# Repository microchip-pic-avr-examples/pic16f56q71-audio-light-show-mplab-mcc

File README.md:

# Audio Light Show Using PIC18-Q71

This project shows the functionality behind a real-time audio processing light show built extremely efficiently on a PIC18-Q71 microcontroller (MCU). 90% of the functionality runs on the MCU without engaging the CPU through the use of various Core-Independent Peripherals (CIPs).

The PIC18-Q71 on-chip analog, consisting of the Operational Amplifier ([OPA](https://www.microchip.com/en-us/products/microcontrollers-and-microprocessors/8-bit-mcus/core-independent-and-analog-peripherals/integrated-analog/operational-amplifier)) and Analog-to-Digital Converter ([ADC](https://www.microchip.com/en-us/products/microcontrollers-and-microprocessors/8-bit-mcus/core-independent-and-analog-peripherals/integrated-analog/analog-to-digital-converter)) modules, measure the incoming analog frequencies and use Direct Memory Access ([DMA](https://www.microchip.com/en-us/products/microcontrollers-and-microprocessors/8-bit-mcus/core-independent-and-analog-peripherals/system-flexibility/direct-memory-access)) to transfer the readings into the Universal Asynchronous Receiver and Transmitter ([UART](https://www.microchip.com/en-us/products/microcontrollers-and-microprocessors/8-bit-mcus/core-independent-and-analog-peripherals/communication-connectivity-peripherals/uart-peripherals))/[DMX512](https://www.microchip.com/en-us/products/microcontrollers-and-microprocessors/8-bit-mcus/core-independent-and-analog-peripherals/communication-connectivity-peripherals/uart-peripherals) module to transmit to the receivers. Each receiver also uses a PIC18-Q71 to receive the DMX data and then appropriately drives WS2812 LEDs through its Serial Peripherals Interface ([SPI](https://www.microchip.com/en-us/products/microcontrollers-and-microprocessors/8-bit-mcus/core-independent-and-analog-peripherals/communication-connectivity-peripherals/spi-peripherals)) module. The receivers are daisy-chained through ethernet cables that transfer both data and power.

The first image below displays seven receviers responding to music, while the other one shows a standby effect. The transmitter has an AUX cable plugged in off-screen.

## Related Documentation

- [PIC18-Q71 Data Sheet](https://ww1.microchip.com/downloads/aemDocuments/documents/MCU08/ProductDocuments/DataSheets/PIC18F26-46-56Q71-Microcontroller-Data-Sheet-DS40002329.pdf)
- [TB3204 - DMX-512 using the UART with Protocol Support](https://ww1.microchip.com/downloads/en/Appnotes/TB3204-DMX-512-using-UART-90003204A.pdf) - Setting up DMX with DMA on a PIC18
- [PIC18F56Q71 Curiosity Nano Hardware User Guide](https://ww1.microchip.com/downloads/aemDocuments/documents/MCU08/ProductDocuments/UserGuides/PIC18F56Q71-CuriosityNano-HW-UG-DS50003481.pdf) - Development tools documentation
- [MIC28517 Data Sheet](https://ww1.microchip.com/downloads/aemDocuments/documents/APID/ProductDocuments/DataSheets/MIC28517-Data-Sheet-DS20006317C.pdf) - Voltage Converter Data Sheet 

## Software Used

- [MPLAB® X IDE 6.1.5](https://www.microchip.com/en-us/development-tools-tools-and-software/mplab-x-ide?utm_source=GitHub&utm_medium=TextLink&utm_campaign=MCU8_MMTCha_MPAE_Examples&utm_content=pic16f56q71-dmx-light-show-github) or newer
- [MPLAB XC8 2.45.0](https://www.microchip.com/en-us/development-tools-tools-and-software/mplab-xc-compilers?utm_source=GitHub&utm_medium=TextLink&utm_campaign=MCU8_MMTCha_MPAE_Examples&utm_content=pic16f56q71-dmx-light-show-github) or newer
- [MPLAB Code Configurator (MCC) 3.95.0](https://www.microchip.com/mplab/mplab-code-configurator) or newer

## Setup

To operate the demo, connect all the transmitters and receivers with an Ethernet cable. Power up the transmitter with a 48V power supply and connect an AUX cable to watch the incoming audio signal come to life. Each receiver is selectively listening to specific DMX data. A DIP switch on each receiver dictates what incoming DMX data to listen to, effectively defining a node number.

Apart from the final transmitter and receiver boards shown in the initial image representations, 3D printed stands are also shown which are used to mount the receiver boards and the diffusing tubes. The diffusing tubes consist of WS2812 LEDs taped to an aluminum strip for support. Inside the fluorescent tube guard, parchment paper lines the interiors and a 3D printed cap securely holds the aluminum strip towards the back of the tube ensuring optimal LED diffusion.

## Theory of Operation

This demo can be broken up into three portions:
* [Audio Signal Processing](#audio-signal-processing)
* [DMX Data](#dmx-data)
* [Driving the WS2812 LEDs](#driving-the-ws2812-leds)

The distinguishing feature of this project is nearly all of this demo operates without the CPU, and instead using CIPs and the DMA. The CPU's sole task is to run the manually programmed visual effects that convert the acquired frequency data into LED data.

### Audio Signal Processing
To obtain the initial audio data, this project extracts bins of audio frequencies and performs peak detection on each bin giving a value corresponding to the intensity of the audio frequency. Each peak is then visually represented on a different LED tube.

Source: [MSGEQ7 data sheet](https://www.sparkfun.com/datasheets/Components/General/MSGEQ7.pdf)

To extract and acquire these audio frequency bins, analog bandpass filters with an ADC can be used for each desired frequency. Alternatively, an MSGEQ7 chip was used to reduce the number of needed passive components. This chip functions as a bandpass filter, multiplexing between frequencies. The PIC18-Q71 drives the chip to change where the center frequency is and then uses its on-board ADC to sample the peak. The PIC18-Q71's OPA is used in Unity Gain mode to impedance match the output, then the ADC with computation is used to acquire the output peak.

By using the OPA in Unity Gain mode, a buffer is created that ensures the ADC can read the analog signal without affecting it. If the input from the filters is of high impedance, the ADC may not read the result accurately. By using the OPA as a buffer, this ensures the ADC can always read the signal accurately and without affecting the original signal. Also, the ADC has built-in computation that provides an automatic average of readings to eliminate potential outliers, providing a more accurate reading.

### DMX Data
DMX512, or DMX for short, is an industry-standard protocol commonly used to control stage lighting and theatrical effects, providing centralized control of multiple devices from a single controller. Devices in a DMX network are daisy-chained together creating a "DMX universe". Within each universe, each node listens to the start code and specific data bytes out of the 512 bytes in each packet.

For this DMX light show, each node listens to 3 bytes and the start code. Depending on the start code, the nodes interpret their three bytes differently, giving DMX flexibility on the fly.

| Start Code | Mode | Byte 1 | Byte 2 | Byte 3 |
| ---- | ---- | ---- | ---- | ---- |
| 2 | Reactive | G LED Data  | R LED Data | B LED Data |
| 3 | Visualizer | # of LEDs to Turn On | Color Change Threshold 1 | Color Change Threshold 2 |

 When `Start Code = 2`, each byte represents the entire tube's RGB data. For the first receiver, when `Start Code = 2` and the data are as shown above (`G = 255, R = 0, B = 0`), the tube looks like in the left image. When `Start Code = 3`, the data interpretation is altered to the table below and the tube for receiver 1 changes to what is shown in the image on the right.

DMX provides the needed structure for fast and flexible data. The PIC18-Q71 compliments DMX by allowing the data's meaning to be changed based on Input/Output (I/O). The data interpretation is changed by toggling a switch, which changes the start code.

### Driving the WS2812 LEDs
After the DMX data has been received, the WS2812 LEDs change to reflect the incoming data. WS2812 LEDs are programmable through a 1-Wire protocol. The LEDs are daisy-chained together, similar to the DMX protocol, but each LED receives all the data, strips off its portion, and sends the data onward. The data for each LED consists of one byte for G, R, and B data respectively (for a total of three bytes).

To drive the WS2812 protocol, the microcontroller pulls a line high or low for different amounts of time:

This requires an I/O line to be changed every 220 ns or at least 4.5 million times per second requiring 4.5 Mhz of processing power. This could create a processing bottleneck in time-sensitive applications. Alternatively, the SPI module of the PIC18-Q71 device family can creatively drive the WS2812 protocol in hardware, so that the MCU simply needs to load the SPI buffer with multiple data bytes instead of individually driving each bit. This is done by chaining the SPI module with the PWM and Configurable Logic Cell (CLC) CIPs to create the serial output needed by the WS2812 protocol.

*SPI + PWM + CLC Waveform*

Implementation with CLC's - Generating 0's

Implementation with CLC's - Generating 1's

## Development Hardware Used

For a large-scale project that shows many moving parts working together, it helps to first set up using easy-to-use hardware, then transition to something more polished and stable.

This project was first set up using [Curiosity Development boards](https://www.microchip.com/en-us/tools-resources/evaluation-boards/curiosity) and jumper wires. Curiosity Development boards feature an on-board programmer, meaning that only a USB cable was needed to program each PIC18-Q71. As the features were developed and the hardware requirements stopped changing, the project was transitioned to dedicated PCBs. Below is the main hardware used for the initial prototype.

- PIC18F56Q71 Curiosity Nano ([EV01G21A](https://www.microchip.com/en-us/development-tool/EV01G21A))
- Curiosity Nano Base for Click Boards™ ([AC164162](https://www.microchip.com/en-us/development-tool/ac164162))
- [MSGEQ7 Graphic Equalizer Display Filter](https://www.sparkfun.com/products/10468)
- [WS2812 LED Strip](https://www.amazon.com/BTF-LIGHTING-Waterproof-Flexible-Individually-Addressable/dp/B01CDTEEZ2/)

The perfboard held the supporting circuitry for the MSGEQ7 to acquire the analog signal. After the analog signal was acquired, a single-ended signal transmitted the DMX data to the receiver board which drive the WS2812 LED, as shown on the left. One other notable point is the Curiosity Nanos all needed to connect to A/C power, greatly limiting the decentralized nature of the daisy-chained DMX protocol. The PIC18F56Q71 was used since it is the family variation used on the Curiosity Nano boards, but any PIC18-Q71 can be used for the project, provided the pin output settings were changed in the code.

The final design was built on PCBs that encoded the DMX signal per the DMX specification, using RS-485 differential signaling for signal integrity of up to 4,000 feet. Also, instead of using XLR cables for the DMX signal, Ethernet cables were used, enabling Power over Ethernet (PoE) to be run through the same cable, eliminating the central power source requirement. This allows only one connection to a power source and large cable runs for the demo to be set up across a stage or even a room - perfect for traveling musicians who need to set up and tear down their equipment quickly.

## Final Hardware Used

- [MPLAB PICkit™ 5 In-Circuit Debugger](https://www.microchip.com/en-us/development-tool/pg164150)

### The Transmitter
The transmitter was built on a custom 4-layer PCB. All parts used are in the [Transmitter Bill of Materials](./PCBs/DMX%20Transmitter/dmxTxBOM.csv) in this repository, as well as all of the corresponding [files needed to have the boards manufactured](./PCBs/DMX%20Transmitter/dmxTx-Outputs.zip). Similar to the prototype hardware, the audio signal comes in and the PIC18-Q71 processes it and sends out the DMX data, but this time, it does so on an Ethernet cable. As noted above, passive PoE was implemented so a 48V power source is used and a MIC28517 buck converter steps down the voltage to the MCU's required five volts.

Notable parts in each of the section of the board:

## Analog In
 The [MSGEQ7](https://www.sparkfun.com/products/10468) extracts the amplitudes of seven frequency bands from an audio signal to be displayed.

## PIC18-Q71
The [PIC18-Q71](https://www.microchip.com/en-us/products/microcontrollers-and-microprocessors/8-bit-mcus/pic-mcus/pic18-q71) drives and reads the MSGEQ7 output by first matching the analog impedance using its on-chip OPA as a unity gain buffer, then sampling the signal using its ADC. It then sends out lighting data to each of the receiver nodes over DMX.

## 48 to 5V
The [MIC28517](https://www.microchip.com/en-us/product/mic28517) was chosen since it can handle the 48V requirements of PoE while providing up to 8A. Each receiver node needs up to 1.5A for the WS2812 LEDs, so this chip gives us plenty of overhead.

## SP485
This chip converts the outgoing DMX signal into a differential pair (RS-485) for increased signal distance (U3 on schematic).

### The Receivers
The receiver [Bill of Materials](./PCBs/DMX%20Receiver/dmxRx.csv) and [board files](./PCBs/DMX%20Receiver/dmxRx-v2Outputs.zip) are included in this repository. The receivers function the same as in the prototype, but have Ethernet connectors on either side pass through the power and DMX signals to continue the daisy chain. The PIC18-Q71 on each receiver takes the DMX data in and then appropriately drives the WS2812 LEDs using its CIPs. Each receiver is programmed using a PICkit™ 5 programmer, as opposed to the on-board PKOB programmer on the Curiosity Nanos used during development.

## Summary
This project covered the theory and functional implementation of a real-time audio light show using the PIC18-Q71. It provides the foundation for scaling this idea into a full-scale application or modifying it as needed.

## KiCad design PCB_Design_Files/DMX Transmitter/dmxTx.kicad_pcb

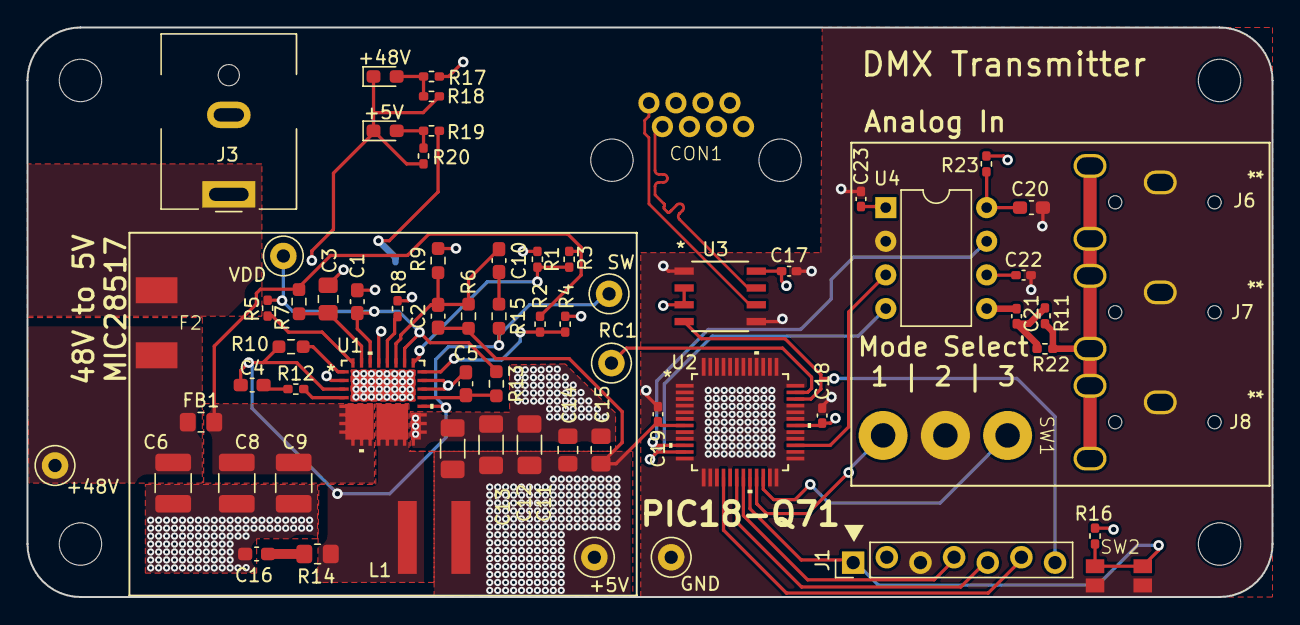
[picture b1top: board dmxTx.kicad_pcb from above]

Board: 4 copper layers, 94.0 x 43.0 mm, 72 parts (1 on the bottom side), 40 nets.

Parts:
C1, C5: 4.7uF; C_0603_1608Metric_Pad1.08x0.95mm_HandSolder
C2: 4700pF; C_0603_1608Metric_Pad1.08x0.95mm_HandSolder
C3: 1uF; C_0805_2012Metric_Pad1.18x1.45mm_HandSolder
C4, C10: 0.1uF; C_0603_1608Metric_Pad1.08x0.95mm_HandSolder
C6, C8, C9: 10uF; C_1210_3225Metric_Pad1.33x2.70mm_HandSolder
C11, C12, C13: 100uF; C_1206_3216Metric_Pad1.33x1.80mm_HandSolder
C14, C15: 22uF; C_0805_2012Metric_Pad1.18x1.45mm_HandSolder
C16: 1000pF; C_0603_1608Metric_Pad1.08x0.95mm_HandSolder
C17, C18, C19, C22, C23: 0.1u; C_0402_1005Metric_Pad0.74x0.62mm_HandSolder
C20: 33p; C_0603_1608Metric_Pad1.08x0.95mm_HandSolder
C21: 0.01u; C_0402_1005Metric_Pad0.74x0.62mm_HandSolder
CON1: E5J88-00LJG2-L
D1: +48V; LED_0603_1608Metric_Pad1.05x0.95mm_HandSolder
D2: +5V; LED_0603_1608Metric_Pad1.05x0.95mm_HandSolder
F1: High Amp; 0679L9100-05
F2: Low Amp; 0679L9100-05
FB1: 120R; R_0805_2012Metric_Pad1.20x1.40mm_HandSolder
H1, H2, H3, H4: MountingHole; MountingHole_3.2mm_M3
J1: Conn_01x07_Socket; PinHeader_1x07_P2.54mm_Vertical
J3: Jack-DC; BarrelJack_CUI_PJ-063AH_Horizontal
J6, J7, J8: STX-3000; STX-3000_KYC
L1: 3.3uH; XGL6060
R1: 300k; R_0402_1005Metric_Pad0.72x0.64mm_HandSolder
R2, R3, R5: 100k; R_0402_1005Metric_Pad0.72x0.64mm_HandSolder
R4, R8, R12: 0R; R_0402_1005Metric_Pad0.72x0.64mm_HandSolder
R6: 10k; R_0603_1608Metric_Pad0.98x0.95mm_HandSolder
R7, R13: 1R; R_0603_1608Metric_Pad0.98x0.95mm_HandSolder
R9: 1.37k; R_0603_1608Metric_Pad0.98x0.95mm_HandSolder
R10: 3.01k; R_0603_1608Metric_Pad0.98x0.95mm_HandSolder
R11, R22: 11k; R_0402_1005Metric_Pad0.72x0.64mm_HandSolder
R14: 1R; R_0805_2012Metric_Pad1.20x1.40mm_HandSolder
R15: 24.9k; R_0603_1608Metric_Pad0.98x0.95mm_HandSolder
R16: 10k; R_0402_1005Metric_Pad0.72x0.64mm_HandSolder
R17, R19: 1k; R_0402_1005Metric_Pad0.72x0.64mm_HandSolder
R18: 47; R_0402_1005Metric_Pad0.72x0.64mm_HandSolder
R20: 790; R_0402_1005Metric_Pad0.72x0.64mm_HandSolder
R23: 200k; R_0402_1005Metric_Pad0.72x0.64mm_HandSolder
SW1: SW_SPDT_MSM; 100AWDP1T2B4M2QE
SW2: MCLR_SW; EVQ-P7A01P
TP1: SW; TestPoint_Loop_D2.50mm_Drill1.0mm
TP2: VDD; TestPoint_Loop_D2.50mm_Drill1.0mm
TP3: RC1; TestPoint_Loop_D2.50mm_Drill1.0mm
TP5: +48V; TestPoint_Loop_D2.50mm_Drill1.0mm
TP9: +5V; TestPoint_Loop_D2.50mm_Drill1.0mm
TP10: GND; TestPoint_Loop_D2.50mm_Drill1.0mm
U1: MIC28517T-E/PHA; VQFN32_6X6_3EP_PHA_MCH
U2: PIC18F56Q71-I/PT; TQFP48_PT_MCH
U3: SP485CN-L; NSOIC-8
U4: MSGEQ7; DIP-8_W7.62mm

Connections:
+5V: C2.1, C11.1, C12.1, C13.1, C14.1, C15.1, C17.2, C18.2, C19.2, C23.2, J1.2, L1.2, R6.2, R16.1, R19.2, R23.2, TP9.1, U2.7 (VDD), U2.30 (VDD), U3.2 (*RE), U3.3 (DE), U3.8 (VCC), U4.1 (VDD)
+48V: C6.1, F2.2, FB1.1, TP5.1
+48V_Hi_Amp: CON1.6, CON1.7, CON1.8, F1.2, R17.2
AGND: C1.2, C3.2, C5.2, C6.2, C8.2, C9.2, C11.2, C12.2, C13.2, C14.2, C15.2, C16.2, C17.1, C18.1, C19.1, C20.1, C22.2, C23.1, CON1.3, CON1.4, CON1.5, D1.1 (K), D2.1 (K), J1.3, J3.2, J6.1, J7.1, J8.1, R1.2, R4.1, R8.1, R9.1, R18.1, R20.1, SW1.2, SW2.2, TP10.1, U1.2 (PGND), U1.16 (PGND), U1.17 (PGND), U1.18 (PGND), U1.19 (PGND), U1.22 (PGND), U1.23 (EXTVDD), U1.29 (PGND), U1.33 (PGND), U1.EP19 (PGND), U2.1 (RC7), U2.2 (RD4), U2.3 (RD5), U2.4 (RD6), U2.5 (RD7), U2.6 (VSS), U2.8 (RB0), U2.9 (RB1), U2.12 (RF4), U2.13 (RF5), U2.14 (RF6), U2.15 (RF7), U2.17 (RB5), U2.23 (RA2), U2.24 (RA3), U2.25 (RA4), U2.26 (RA5), U2.28 (RE1), U2.29 (RE2), U2.31 (VSS), U2.32 (RA7), U2.33 (RA6), U2.36 (RF0), U2.37 (RF1), U2.38 (RF2), U2.39 (RF3), U2.40 (RC2), U2.41 (RC3), U2.42 (RD0), U2.43 (RD1), U2.44 (RD2), U2.45 (RD3), U2.46 (RC4), U2.47 (RC5), U2.48 (RC6), U3.1 (RO), U3.5 (GND), U4.2 (VSS)
AN_OUT: U2.27 (RE0), U4.3 (OUT)
AUDIO_IN: J6.2, J6.3, J7.2, J7.3, J8.2, J8.3, R11.1, R22.1
D+: CON1.1, U3.6 (A)
D-: CON1.2, U3.7 (B)
DMX OUT: J1.7, U2.34 (RC0), U3.4 (DI)
FB: C2.2, C10.2, R6.1, R9.2, U1.27 (FB)
ICSPCLK: J1.5, U2.18 (RB6/ICSPCLK)
ICSPDAT: J1.4, U2.19 (RB7/ICSPDAT)
ILIM: R10.2, U1.1 (ILIM)
MCLR: J1.1, R16.2, SW2.1, U2.20 (RE3/*MCLR/VPP)
MODE1: SW1.1, U2.21 (RA0)
MODE2: SW1.3, U2.22 (RA1)
unnamed: C4.1, R12.1
unnamed: C10.1, R15.1
unnamed: C16.1, R14.1
unnamed: C21.1, R11.2, R22.2
unnamed: D1.2 (A), R17.1, R18.2
unnamed: D2.2 (A), R19.1, R20.2
unnamed: F1.1, F2.1, J3.1
unnamed: R12.2, U1.4 (BST)
unnamed: R2.2, R4.2, U1.24 (EN)
unnamed: R1.1, R3.2, U1.25 (FREQ)
unnamed: R5.1, U1.32 (PG)
unnamed: R8.2, U1.28 (AGND)
unnamed: C5.1, R13.2, U1.21 (PVDD)
unnamed: C3.1, R7.2, U1.31 (SVIN)
unnamed: TP3.1, U2.35 (RC1)
unnamed: C20.2, R23.1, U4.8 (CKIN)
unnamed: C22.1, U4.6 (GND)
unnamed: C21.2, U4.5 (IN)
RESET: U2.10 (RB2), U4.7 (RESET)
STROBE: U2.11 (RB3), U4.4 (STROBE)
SW: C4.2, L1.1, R10.1, R14.2, R15.2, TP1.1, U1.3 (SW), U1.12 (SW), U1.13 (SW), U1.14 (SW), U1.15 (SW), U1.20 (SW), U1.EP12 (SW)
U1TX: J1.6, U2.16 (RB4)
VDD: C1.1, R5.2, R13.1, TP2.1, U1.26 (MODE), U1.30 (VDD)
VIN: C8.1, C9.1, FB1.2, R2.1, R3.1, R7.1, U1.5 (PVIN), U1.6 (PVIN), U1.7 (PVIN), U1.8 (PVIN), U1.9 (PVIN), U1.10 (PVIN), U1.11 (PVIN), U1.EP5 (PVIN)

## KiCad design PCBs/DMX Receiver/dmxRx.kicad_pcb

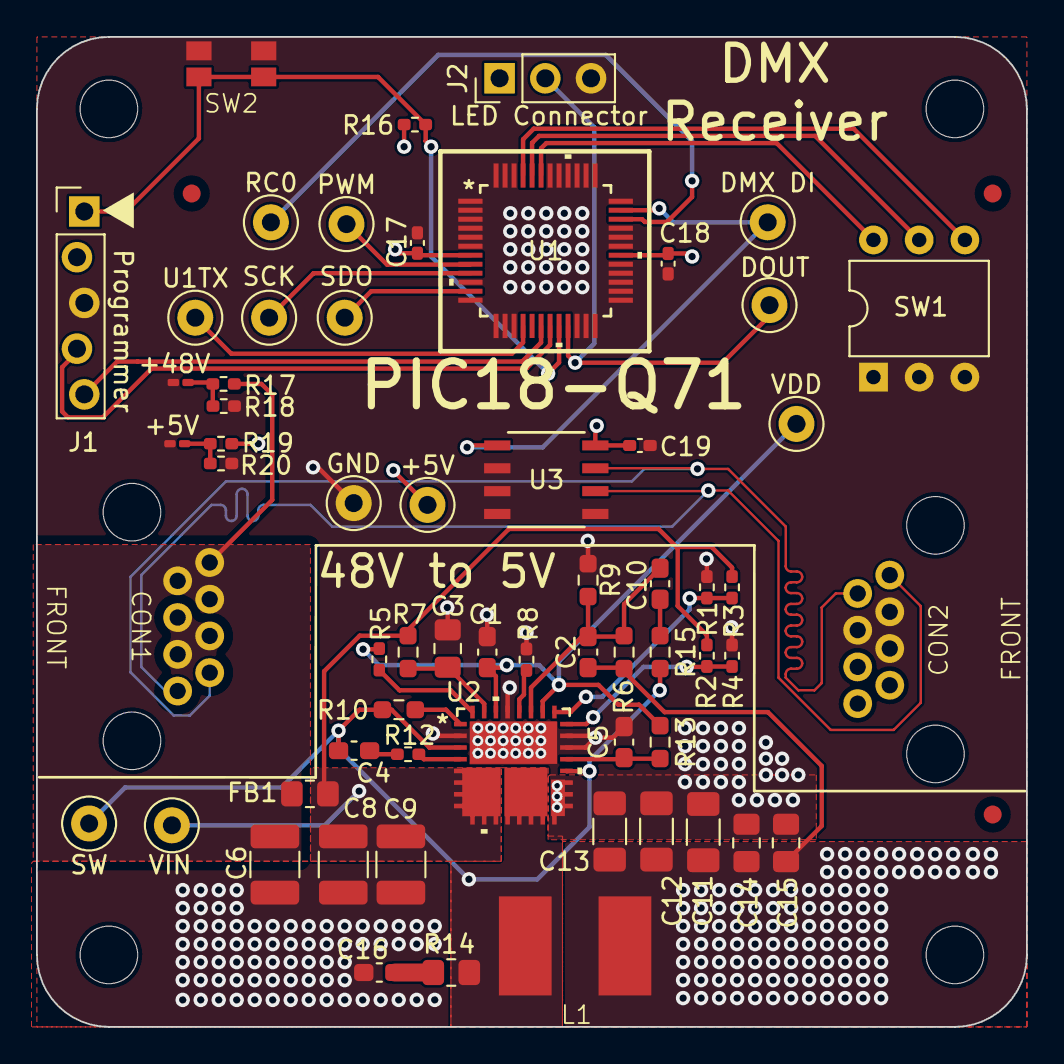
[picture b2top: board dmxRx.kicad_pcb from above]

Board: 4 copper layers, 55.0 x 55.0 mm, 69 parts (0 on the bottom side), 35 nets.

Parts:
C1, C5: 4.7uF; C_0603_1608Metric_Pad1.08x0.95mm_HandSolder
C2: 4700pF; C_0603_1608Metric_Pad1.08x0.95mm_HandSolder
C3: 1uF; C_0805_2012Metric_Pad1.18x1.45mm_HandSolder
C4, C10: 0.1uF; C_0603_1608Metric_Pad1.08x0.95mm_HandSolder
C6, C8, C9: 10uF; C_1210_3225Metric_Pad1.33x2.70mm_HandSolder
C11, C12, C13: 100uF; C_1206_3216Metric_Pad1.33x1.80mm_HandSolder
C14, C15: 22uF; C_0805_2012Metric_Pad1.18x1.45mm_HandSolder
C16: 1000pF; C_0603_1608Metric_Pad1.08x0.95mm_HandSolder
C17, C18, C19: .1uF; C_0402_1005Metric_Pad0.74x0.62mm_HandSolder
CON1, CON2: E5J88-00LJG2-L
D1: +48V; R_0201_0603Metric_Pad0.64x0.40mm_HandSolder
D2: +5V; R_0201_0603Metric_Pad0.64x0.40mm_HandSolder
FB1: 120R; R_0805_2012Metric_Pad1.20x1.40mm_HandSolder
FID1, FID2, FID3: Fiducial; Fiducial_1mm_Mask2mm
H1, H2, H3, H4: MountingHole; MountingHole_3.2mm_M3
J1: Conn_01x05_Socket; PinHeader_1x05_P2.54mm_Vertical
J2: Conn_01x03_Socket; PinHeader_1x03_P2.54mm_Vertical
L1: 3.3uH; XGL6060
R1: 300k; R_0402_1005Metric_Pad0.72x0.64mm_HandSolder
R2, R3, R5: 100k; R_0402_1005Metric_Pad0.72x0.64mm_HandSolder
R4, R8, R12: 0R; R_0402_1005Metric_Pad0.72x0.64mm_HandSolder
R6: 10k; R_0603_1608Metric_Pad0.98x0.95mm_HandSolder
R7, R13: 1R; R_0603_1608Metric_Pad0.98x0.95mm_HandSolder
R9: 1.37k; R_0603_1608Metric_Pad0.98x0.95mm_HandSolder
R10: 3.01k; R_0603_1608Metric_Pad0.98x0.95mm_HandSolder
R14: 1R; R_0805_2012Metric_Pad1.20x1.40mm_HandSolder
R15: 24.9k; R_0603_1608Metric_Pad0.98x0.95mm_HandSolder
R16: 10k; R_0402_1005Metric_Pad0.72x0.64mm_HandSolder
R17: 30k; R_0402_1005Metric_Pad0.72x0.64mm_HandSolder
R18: 1.4k; R_0402_1005Metric_Pad0.72x0.64mm_HandSolder
R19: 1k; R_0402_1005Metric_Pad0.72x0.64mm_HandSolder
R20: 790; R_0402_1005Metric_Pad0.72x0.64mm_HandSolder
SW1: SW_DIP_x03; DIP-6_W7.62mm
SW2: MCLR_SW; EVQ-P7A01P
TP1: PWM; TestPoint_Loop_D2.50mm_Drill1.0mm
TP2: SCK; TestPoint_Loop_D2.50mm_Drill1.0mm
TP3: SDO; TestPoint_Loop_D2.50mm_Drill1.0mm
TP4: U1TX; TestPoint_Loop_D2.50mm_Drill1.0mm
TP5: DOUT; TestPoint_Loop_D2.50mm_Drill1.0mm
TP6: DMX DI; TestPoint_Loop_D2.50mm_Drill1.0mm
TP7: GND; TestPoint_Loop_D2.50mm_Drill1.0mm
TP8: +5V; TestPoint_Loop_D2.50mm_Drill1.0mm
TP9: VIN; TestPoint_Loop_D2.50mm_Drill1.0mm
TP10: RC0; TestPoint_Loop_D2.50mm_Drill1.0mm
TP11: SW; TestPoint_Loop_D2.50mm_Drill1.0mm
TP12: VDD; TestPoint_Loop_D2.50mm_Drill1.0mm
U1: PIC18F56Q71-I/PT; TQFP48_PT_MCH
U2: MIC28517T-E/PHA; VQFN32_6X6_3EP_PHA_MCH
U3: SP485CN-L; NSOIC-8

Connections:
+5V: C2.1, C11.1, C12.1, C13.1, C14.1, C15.1, C17.2, C18.2, C19.2, J1.2, J2.1, L1.2, R6.2, R16.1, R19.2, TP8.1, U1.7 (VDD), U1.30 (VDD), U3.8 (VCC)
+48V: C6.1, CON1.1, CON1.2, CON1.3, CON2.1, CON2.2, CON2.3, FB1.1, R17.2
D+: CON1.8, CON2.8, U3.6 (A)
D-: CON1.7, CON2.7, U3.7 (B)
DMX DATA IN: TP6.1, U1.35 (RC1), U3.1 (RO)
DOUT: J2.2, TP5.1, U1.21 (RA0)
FB: C2.2, C10.2, R6.1, R9.2, U2.27 (FB)
GND: C1.2, C3.2, C5.2, C6.2, C8.2, C9.2, C11.2, C12.2, C13.2, C14.2, C15.2, C16.2, C17.1, C18.1, C19.1, CON1.4, CON1.5, CON1.6, CON2.4, CON2.5, CON2.6, D1.1 (K), D2.1 (K), J1.3, J2.3, R1.2, R4.1, R8.1, R9.1, R18.1, R20.1, SW1.1, SW1.2, SW1.3, SW2.2, TP7.1, U1.1 (RC7), U1.2 (RD4), U1.3 (RD5), U1.4 (RD6), U1.5 (RD7), U1.6 (VSS), U1.10 (RB2), U1.12 (RF4), U1.13 (RF5), U1.14 (RF6), U1.15 (RF7), U1.22 (RA1), U1.23 (RA2), U1.24 (RA3), U1.25 (RA4), U1.26 (RA5), U1.27 (RE0), U1.28 (RE1), U1.29 (RE2), U1.31 (VSS), U1.32 (RA7), U1.33 (RA6), U1.36 (RF0), U1.37 (RF1), U1.38 (RF2), U1.39 (RF3), U1.40 (RC2), U1.41 (RC3), U1.42 (RD0), U1.46 (RC4), U1.47 (RC5), U1.48 (RC6), U2.2 (PGND), U2.16 (PGND), U2.17 (PGND), U2.18 (PGND), U2.19 (PGND), U2.22 (PGND), U2.23 (EXTVDD), U2.29 (PGND), U2.33 (PGND), U2.EP19 (PGND), U3.2 (*RE), U3.3 (DE), U3.4 (DI), U3.5 (GND)
ICSPCLK: J1.5, U1.18 (RB6/ICSPCLK)
ICSPDAT: J1.4, U1.19 (RB7/ICSPDAT)
ILIM: R10.2, U2.1 (ILIM)
MCLR: J1.1, R16.2, SW2.1, U1.20 (RE3/*MCLR/VPP)
unnamed: C4.1, R12.1
unnamed: C10.1, R15.1
unnamed: C16.1, R14.1
unnamed: D1.2 (A), R17.1, R18.2
unnamed: D2.2 (A), R19.1, R20.2
unnamed: TP1.1, U1.8 (RB0)
unnamed: TP2.1, U1.9 (RB1)
unnamed: TP3.1, U1.11 (RB3)
unnamed: TP4.1, U1.16 (RB4)
unnamed: TP10.1, U1.34 (RC0)
unnamed: SW1.6, U1.43 (RD1)
unnamed: SW1.5, U1.44 (RD2)
unnamed: SW1.4, U1.45 (RD3)
unnamed: R12.2, U2.4 (BST)
unnamed: R2.2, R4.2, U2.24 (EN)
unnamed: R1.1, R3.2, U2.25 (FREQ)
unnamed: R5.1, U2.32 (PG)
unnamed: R8.2, U2.28 (AGND)
unnamed: C5.1, R13.2, U2.21 (PVDD)
unnamed: C3.1, R7.2, U2.31 (SVIN)
SW: C4.2, L1.1, R10.1, R14.2, R15.2, TP11.1, U2.3 (SW), U2.12 (SW), U2.13 (SW), U2.14 (SW), U2.15 (SW), U2.20 (SW), U2.EP12 (SW)
VDD: C1.1, R5.2, R13.1, TP12.1, U2.26 (MODE), U2.30 (VDD)
VIN: C8.1, C9.1, FB1.2, R2.1, R3.1, R7.1, TP9.1, U2.5 (PVIN), U2.6 (PVIN), U2.7 (PVIN), U2.8 (PVIN), U2.9 (PVIN), U2.10 (PVIN), U2.11 (PVIN), U2.EP5 (PVIN)

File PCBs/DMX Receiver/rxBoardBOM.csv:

Source:,C:\Users\user\Desktop\mchp_dmx\PCBs\DMX Receiver\dmxRx.kicad_sch,,,,,,
Date:,9/14/2023 9:39,,DNP,,,,bag 1
Tool:,Eeschema 7.0.6,,,,,,bag 2
Generator:,C:\Program Files\KiCad\7.0\bin\scripting\plugins/bom_csv_grouped_by_value_with_fp.py,,,,,,
Component Count:,66,,,,,,
Ref,Qnty,Value,Cmp name,Footprint,Description,Vendor,DNP
"C1, C5",2,4.7uF,C,Capacitor_SMD:C_0603_1608Metric_Pad1.08x0.95mm_HandSolder,Unpolarized capacitor,https://www.digikey.com/en/products/detail/murata-electronic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,
C2,1,4700pF,C,Capacitor_SMD:C_0603_1608Metric_Pad1.08x0.95mm_HandSolder,Unpolarized capacitor,https://www.digikey.com/en/products/detail/kemet/C0603C472K5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,
C3,1,1uF,C,Capacitor_SMD:C_0805_2012Metric_Pad1.18x1.45mm_HandSolder,Unpolarized capacitor,https://www.digikey.com/en/products/detail/murata-electronic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,
"C4, C10",2,0.1uF,C,Capacitor_SMD:C_0603_1608Metric_Pad1.08x0.95mm_HandSolder,Unpolarized capacitor,https://www.digikey.com/en/products/detail/w%C3%BCrth-elektr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,
"C6, C8, C9",3,10uF,C,Capacitor_SMD:C_1210_3225Metric_Pad1.33x2.70mm_HandSolder,Unpolarized capacitor,https://www.digikey.com/en/products/detail/murata-electronic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,
"C11, C12, C13",3,100uF,C,Capacitor_SMD:C_1206_3216Metric_Pad1.33x1.80mm_HandSolder,Unpolarized capacitor,https://www.digikey.com/en/products/detail/samsung-electro-m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,
"C14, C15",2,22uF,C,Capacitor_SMD:C_0805_2012Metric_Pad1.18x1.45mm_HandSolder,Unpolarized capacitor,https://www.digikey.com/en/products/detail/murata-electronic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,
C16,1,1000pF,C,Capacitor_SMD:C_0603_1608Metric_Pad1.08x0.95mm_HandSolder,Unpolarized capacitor,https://www.digikey.com/en/products/detail/w%C3%BCrth-elektr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,
"C17, C18, C19",3,.1uF,C,Capacitor_SMD:C_0402_1005Metric_Pad0.74x0.62mm_HandSolder,Unpolarized capacitor,https://www.digikey.com/en/products/detail/samsung-electro-m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,
"CON1, CON2",2,~,E5J88-00LJG2-L,E5J88-00LJG2-L:E5J88-00LJG2-L,,https://www.digikey.com/en/products/detail/pulse-electronics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,
D1,1,+48V,LED,Resistor_SMD:R_0201_0603Metric_Pad0.64x0.40mm_HandSolder,Light emitting diode,https://www.digikey.com/en/products/detail/liteon/LTST-C191K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,
D2,1,+5V,LED,Resistor_SMD:R_0201_0603Metric_Pad0.64x0.40mm_HandSolder,Light emitting diode,https://www.digikey.com/en/products/detail/liteon/LTST-C190G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,
FB1,1,120R,FerriteBead,Resistor_SMD:R_0805_2012Metric_Pad1.20x1.40mm_HandSolder,Ferrite bead,https://www.digikey.com/en/products/detail/vishay-dale/ILHB0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,
"H1, H2, H3, H4",4,MountingHole,MountingHole,MountingHole:MountingHole_3.2mm_M3,Mounting Hole without connection,N/A,
J1,1,Conn_01x05_Socket,Conn_01x05_Socket,Connector_PinHeader_2.54mm:PinHeader_1x05_P2.54mm_Vertical,"Generic connector, single row, 01x05, script generated",https://www.digikey.com/en/products/detail/w%C3%BCrth-elektr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,
J2,1,Conn_01x03_Socket,Conn_01x03_Socket,Connector_PinHeader_2.54mm:PinHeader_1x03_P2.54mm_Vertical,"Generic connector, single row, 01x03, script generated",https://www.digikey.com/en/products/detail/w%C3%BCrth-elektr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,
L1,1,3.3uH,L,XGL6060:XGL6060,Inductor,https://www.digikey.com/en/products/detail/coilcraft/XGL6060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,
R1,1,300k,R,Resistor_SMD:R_0402_1005Metric_Pad0.72x0.64mm_HandSolder,Resistor,https://www.digikey.com/en/products/detail/panasonic-electro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,
"R2, R3, R5",3,100k,R,Resistor_SMD:R_0402_1005Metric_Pad0.72x0.64mm_HandSolder,Resistor,https://www.digikey.com/en/products/detail/koa-speer-electro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,
R4,1,0R,R,Resistor_SMD:R_0402_1005Metric_Pad0.72x0.64mm_HandSolder,Resistor,https://www.digikey.com/en/products/detail/koa-speer-electro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,DNP
R6,1,10k,R,Resistor_SMD:R_0603_1608Metric_Pad0.98x0.95mm_HandSolder,Resistor,https://www.digikey.com/en/products/detail/yageo/AC0603FR-10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,
"R7, R13",2,1R,R,Resistor_SMD:R_0603_1608Metric_Pad0.98x0.95mm_HandSolder,Resistor,https://www.digikey.com/en/products/detail/stackpole-electro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,
"R8, R12",2,0R,R,Resistor_SMD:R_0402_1005Metric_Pad0.72x0.64mm_HandSolder,Resistor,https://www.digikey.com/en/products/detail/panasonic-electro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,
R9,1,1.37k,R,Resistor_SMD:R_0603_1608Metric_Pad0.98x0.95mm_HandSolder,Resistor,https://www.digikey.com/en/products/detail/yageo/RC0603FR-07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,
R10,1,3.01k,R,Resistor_SMD:R_0603_1608Metric_Pad0.98x0.95mm_HandSolder,Resistor,https://www.digikey.com/en/products/detail/yageo/RC0603FR-07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,
R14,1,1R,R,Resistor_SMD:R_0805_2012Metric_Pad1.20x1.40mm_HandSolder,Resistor,https://www.digikey.com/en/products/detail/stackpole-electro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,
R15,1,24.9k,R,Resistor_SMD:R_0603_1608Metric_Pad0.98x0.95mm_HandSolder,Resistor,https://www.digikey.com/en/products/detail/yageo/RC0603FR-07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,
R16,1,10k,R,Resistor_SMD:R_0402_1005Metric_Pad0.72x0.64mm_HandSolder,Resistor,https://www.digikey.com/en/products/detail/yageo/AC0402FR-07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,
R17,1,30k,R,Resistor_SMD:R_0402_1005Metric_Pad0.72x0.64mm_HandSolder,Resistor,https://www.digikey.com/en/products/detail/yageo/RC0805JR-07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,
R18,1,1.4k,R,Resistor_SMD:R_0402_1005Metric_Pad0.72x0.64mm_HandSolder,Resistor,https://www.digikey.com/en/products/detail/yageo/RC0805FR-07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,
R19,1,1k,R,Resistor_SMD:R_0402_1005Metric_Pad0.72x0.64mm_HandSolder,Resistor,https://www.digikey.com/en/products/detail/susumu/RR0510P-10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,
R20,1,790,R,Resistor_SMD:R_0402_1005Metric_Pad0.72x0.64mm_HandSolder,Resistor,https://www.digikey.com/en/products/detail/yageo/RC0402FR-07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,
SW1,1,SW_DIP_x03,SW_DIP_x03,Package_DIP:DIP-6_W7.62mm,"3x DIP Switch, Single Pole Single Throw (SPST) switch, small symbol",https://www.digikey.com/en/products/detail/cts-electrocompon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,
SW2,1,MCLR_SW,SW_Push,EVQ-P7A01P:EVQ-P7A01P,"Push button switch, generic, two pins",https://www.digikey.com/en/products/detail/panasonic-electro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,
TP1,1,PWM,TestPoint,TestPoint:TestPoint_Loop_D2.50mm_Drill1.0mm,test point,N/A,
TP2,1,SCK,TestPoint,TestPoint:TestPoint_Loop_D2.50mm_Drill1.0mm,test point,N/A,
TP3,1,SDO,TestPoint,TestPoint:TestPoint_Loop_D2.50mm_Drill1.0mm,test point,N/A,
TP4,1,U1TX,TestPoint,TestPoint:TestPoint_Loop_D2.50mm_Drill1.0mm,test point,N/A,
TP5,1,DOUT,TestPoint,TestPoint:TestPoint_Loop_D2.50mm_Drill1.0mm,test point,N/A,
TP6,1,DMX DI,TestPoint,TestPoint:TestPoint_Loop_D2.50mm_Drill1.0mm,test point,N/A,
TP7,1,GND,TestPoint,TestPoint:TestPoint_Loop_D2.50mm_Drill1.0mm,test point,N/A,
TP8,1,+5V,TestPoint,TestPoint:TestPoint_Loop_D2.50mm_Drill1.0mm,test point,N/A,
"TP9, TP11",2,SW,TestPoint,TestPoint:TestPoint_Loop_D2.50mm_Drill1.0mm,test point,N/A,
TP10,1,RC0,TestPoint,TestPoint:TestPoint_Loop_D2.50mm_Drill1.0mm,test point,N/A,
TP12,1,VDD,TestPoint,TestPoint:TestPoint_Loop_D2.50mm_Drill1.0mm,test point,N/A,
U1,1,PIC18F56Q71-I/PT,PIC18F56Q71-I_PT,TQFP48_PT_MCH,,https://www.digikey.com/en/products/detail/microchip-technol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,
U2,1,MIC28517T-E/PHA,MIC28517T-E_PHA,VQFN32_6X6_3EP_PHA_MCH,,https://www.microchip.com/en-us/product/mic28517,
U3,1,SP485CN-L,SP485CN-L,NSOIC-8,,https://www.digikey.com/en/products/detail/maxlinear-inc/SP4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,

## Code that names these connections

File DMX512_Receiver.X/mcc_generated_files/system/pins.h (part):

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// get/set RA0 aliases
#define IO_RA0_TRIS                 TRISAbits.TRISA0
#define IO_RA0_LAT                  LATAbits.LATA0
#define IO_RA0_PORT                 PORTAbits.RA0
#define IO_RA0_WPU                  WPUAbits.WPUA0
#define IO_RA0_OD                   ODCONAbits.ODCA0
#define IO_RA0_ANS                  ANSELAbits.ANSELA0
#define IO_RA0_SetHigh()            do { LATAbits.LATA0 = 1; } while(0)
#define IO_RA0_SetLow()             do { LATAbits.LATA0 = 0; } while(0)
#define IO_RA0_Toggle()             do { LATAbits.LATA0 = ~LATAbits.LATA0; } while(0)
#define IO_RA0_GetValue()           PORTAbits.RA0
#define IO_RA0_SetDigitalInput()    do { TRISAbits.TRISA0 = 1; } while(0)
#define IO_RA0_SetDigitalOutput()   do { TRISAbits.TRISA0 = 0; } while(0)
#define IO_RA0_SetPullup()          do { WPUAbits.WPUA0 = 1; } while(0)
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// get/set RB0 aliases
#define IO_RB0_TRIS                 TRISBbits.TRISB0
#define IO_RB0_LAT                  LATBbits.LATB0
#define IO_RB0_PORT                 PORTBbits.RB0
#define IO_RB0_WPU                  WPUBbits.WPUB0
#define IO_RB0_OD                   ODCONBbits.ODCB0
#define IO_RB0_ANS                  ANSELBbits.ANSELB0
#define IO_RB0_SetHigh()            do { LATBbits.LATB0 = 1; } while(0)
#define IO_RB0_SetLow()             do { LATBbits.LATB0 = 0; } while(0)
#define IO_RB0_Toggle()             do { LATBbits.LATB0 = ~LATBbits.LATB0; } while(0)
#define IO_RB0_GetValue()           PORTBbits.RB0
#define IO_RB0_SetDigitalInput()    do { TRISBbits.TRISB0 = 1; } while(0)
#define IO_RB0_SetDigitalOutput()   do { TRISBbits.TRISB0 = 0; } while(0)
#define IO_RB0_SetPullup()          do { WPUBbits.WPUB0 = 1; } while(0)
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// get/set RB2 aliases
#define IO_RB2_TRIS                 TRISBbits.TRISB2
#define IO_RB2_LAT                  LATBbits.LATB2
#define IO_RB2_PORT                 PORTBbits.RB2
#define IO_RB2_WPU                  WPUBbits.WPUB2
#define IO_RB2_OD                   ODCONBbits.ODCB2
#define IO_RB2_ANS                  ANSELBbits.ANSELB2
#define IO_RB2_SetHigh()            do { LATBbits.LATB2 = 1; } while(0)
#define IO_RB2_SetLow()             do { LATBbits.LATB2 = 0; } while(0)
#define IO_RB2_Toggle()             do { LATBbits.LATB2 = ~LATBbits.LATB2; } while(0)
#define IO_RB2_GetValue()           PORTBbits.RB2
#define IO_RB2_SetDigitalInput()    do { TRISBbits.TRISB2 = 1; } while(0)
#define IO_RB2_SetDigitalOutput()   do { TRISBbits.TRISB2 = 0; } while(0)
#define IO_RB2_SetPullup()          do { WPUBbits.WPUB2 = 1; } while(0)
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// get/set RB4 aliases
#define IO_RB4_TRIS                 TRISBbits.TRISB4
#define IO_RB4_LAT                  LATBbits.LATB4
#define IO_RB4_PORT                 PORTBbits.RB4
#define IO_RB4_WPU                  WPUBbits.WPUB4
#define IO_RB4_OD                   ODCONBbits.ODCB4
#define IO_RB4_ANS                  ANSELBbits.ANSELB4
#define IO_RB4_SetHigh()            do { LATBbits.LATB4 = 1; } while(0)
#define IO_RB4_SetLow()             do { LATBbits.LATB4 = 0; } while(0)
#define IO_RB4_Toggle()             do { LATBbits.LATB4 = ~LATBbits.LATB4; } while(0)
#define IO_RB4_GetValue()           PORTBbits.RB4
#define IO_RB4_SetDigitalInput()    do { TRISBbits.TRISB4 = 1; } while(0)
#define IO_RB4_SetDigitalOutput()   do { TRISBbits.TRISB4 = 0; } while(0)
#define IO_RB4_SetPullup()          do { WPUBbits.WPUB4 = 1; } while(0)
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// get/set RB5 aliases
#define IO_RB5_TRIS                 TRISBbits.TRISB5
#define IO_RB5_LAT                  LATBbits.LATB5
#define IO_RB5_PORT                 PORTBbits.RB5
#define IO_RB5_WPU                  WPUBbits.WPUB5
#define IO_RB5_OD                   ODCONBbits.ODCB5
#define IO_RB5_ANS                  ANSELBbits.ANSELB5
#define IO_RB5_SetHigh()            do { LATBbits.LATB5 = 1; } while(0)
#define IO_RB5_SetLow()             do { LATBbits.LATB5 = 0; } while(0)
#define IO_RB5_Toggle()             do { LATBbits.LATB5 = ~LATBbits.LATB5; } while(0)
#define IO_RB5_GetValue()           PORTBbits.RB5
#define IO_RB5_SetDigitalInput()    do { TRISBbits.TRISB5 = 1; } while(0)
#define IO_RB5_SetDigitalOutput()   do { TRISBbits.TRISB5 = 0; } while(0)
#define IO_RB5_SetPullup()          do { WPUBbits.WPUB5 = 1; } while(0)
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// get/set RC0 aliases
#define IO_RC0_TRIS                 TRISCbits.TRISC0
#define IO_RC0_LAT                  LATCbits.LATC0
#define IO_RC0_PORT                 PORTCbits.RC0
#define IO_RC0_WPU                  WPUCbits.WPUC0
#define IO_RC0_OD                   ODCONCbits.ODCC0
#define IO_RC0_ANS                  ANSELCbits.ANSELC0
#define IO_RC0_SetHigh()            do { LATCbits.LATC0 = 1; } while(0)
#define IO_RC0_SetLow()             do { LATCbits.LATC0 = 0; } while(0)
#define IO_RC0_Toggle()             do { LATCbits.LATC0 = ~LATCbits.LATC0; } while(0)
#define IO_RC0_GetValue()           PORTCbits.RC0
#define IO_RC0_SetDigitalInput()    do { TRISCbits.TRISC0 = 1; } while(0)
#define IO_RC0_SetDigitalOutput()   do { TRISCbits.TRISC0 = 0; } while(0)
#define IO_RC0_SetPullup()          do { WPUCbits.WPUC0 = 1; } while(0)
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// get/set RD1 aliases
#define IO_RD1_TRIS                 TRISDbits.TRISD1
#define IO_RD1_LAT                  LATDbits.LATD1
#define IO_RD1_PORT                 PORTDbits.RD1
#define IO_RD1_WPU                  WPUDbits.WPUD1
#define IO_RD1_OD                   ODCONDbits.ODCD1
#define IO_RD1_ANS                  ANSELDbits.ANSELD1
#define IO_RD1_SetHigh()            do { LATDbits.LATD1 = 1; } while(0)
#define IO_RD1_SetLow()             do { LATDbits.LATD1 = 0; } while(0)
#define IO_RD1_Toggle()             do { LATDbits.LATD1 = ~LATDbits.LATD1; } while(0)
#define IO_RD1_GetValue()           PORTDbits.RD1
#define IO_RD1_SetDigitalInput()    do { TRISDbits.TRISD1 = 1; } while(0)
#define IO_RD1_SetDigitalOutput()   do { TRISDbits.TRISD1 = 0; } while(0)
#define IO_RD1_SetPullup()          do { WPUDbits.WPUD1 = 1; } while(0)
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// get/set RD2 aliases
#define IO_RD2_TRIS                 TRISDbits.TRISD2
#define IO_RD2_LAT                  LATDbits.LATD2
#define IO_RD2_PORT                 PORTDbits.RD2
#define IO_RD2_WPU                  WPUDbits.WPUD2
#define IO_RD2_OD                   ODCONDbits.ODCD2
#define IO_RD2_ANS                  ANSELDbits.ANSELD2
#define IO_RD2_SetHigh()            do { LATDbits.LATD2 = 1; } while(0)
#define IO_RD2_SetLow()             do { LATDbits.LATD2 = 0; } while(0)
#define IO_RD2_Toggle()             do { LATDbits.LATD2 = ~LATDbits.LATD2; } while(0)
#define IO_RD2_GetValue()           PORTDbits.RD2
#define IO_RD2_SetDigitalInput()    do { TRISDbits.TRISD2 = 1; } while(0)
#define IO_RD2_SetDigitalOutput()   do { TRISDbits.TRISD2 = 0; } while(0)
#define IO_RD2_SetPullup()          do { WPUDbits.WPUD2 = 1; } while(0)
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// get/set RD3 aliases
#define IO_RD3_TRIS                 TRISDbits.TRISD3
#define IO_RD3_LAT                  LATDbits.LATD3
#define IO_RD3_PORT                 PORTDbits.RD3
#define IO_RD3_WPU                  WPUDbits.WPUD3
#define IO_RD3_OD                   ODCONDbits.ODCD3
#define IO_RD3_ANS                  ANSELDbits.ANSELD3
#define IO_RD3_SetHigh()            do { LATDbits.LATD3 = 1; } while(0)
#define IO_RD3_SetLow()             do { LATDbits.LATD3 = 0; } while(0)
#define IO_RD3_Toggle()             do { LATDbits.LATD3 = ~LATDbits.LATD3; } while(0)
#define IO_RD3_GetValue()           PORTDbits.RD3
#define IO_RD3_SetDigitalInput()    do { TRISDbits.TRISD3 = 1; } while(0)
#define IO_RD3_SetDigitalOutput()   do { TRISDbits.TRISD3 = 0; } while(0)
#define IO_RD3_SetPullup()          do { WPUDbits.WPUD3 = 1; } while(0)
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
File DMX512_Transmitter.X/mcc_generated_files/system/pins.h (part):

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// get/set RA0 aliases
#define IO_RA0_TRIS                 TRISAbits.TRISA0
#define IO_RA0_LAT                  LATAbits.LATA0
#define IO_RA0_PORT                 PORTAbits.RA0
#define IO_RA0_WPU                  WPUAbits.WPUA0
#define IO_RA0_OD                   ODCONAbits.ODCA0
#define IO_RA0_ANS                  ANSELAbits.ANSELA0
#define IO_RA0_SetHigh()            do { LATAbits.LATA0 = 1; } while(0)
#define IO_RA0_SetLow()             do { LATAbits.LATA0 = 0; } while(0)
#define IO_RA0_Toggle()             do { LATAbits.LATA0 = ~LATAbits.LATA0; } while(0)
#define IO_RA0_GetValue()           PORTAbits.RA0
#define IO_RA0_SetDigitalInput()    do { TRISAbits.TRISA0 = 1; } while(0)
#define IO_RA0_SetDigitalOutput()   do { TRISAbits.TRISA0 = 0; } while(0)
#define IO_RA0_SetPullup()          do { WPUAbits.WPUA0 = 1; } while(0)
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// get/set RA1 aliases
#define IO_RA1_TRIS                 TRISAbits.TRISA1
#define IO_RA1_LAT                  LATAbits.LATA1
#define IO_RA1_PORT                 PORTAbits.RA1
#define IO_RA1_WPU                  WPUAbits.WPUA1
#define IO_RA1_OD                   ODCONAbits.ODCA1
#define IO_RA1_ANS                  ANSELAbits.ANSELA1
#define IO_RA1_SetHigh()            do { LATAbits.LATA1 = 1; } while(0)
#define IO_RA1_SetLow()             do { LATAbits.LATA1 = 0; } while(0)
#define IO_RA1_Toggle()             do { LATAbits.LATA1 = ~LATAbits.LATA1; } while(0)
#define IO_RA1_GetValue()           PORTAbits.RA1
#define IO_RA1_SetDigitalInput()    do { TRISAbits.TRISA1 = 1; } while(0)
#define IO_RA1_SetDigitalOutput()   do { TRISAbits.TRISA1 = 0; } while(0)
#define IO_RA1_SetPullup()          do { WPUAbits.WPUA1 = 1; } while(0)
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// get/set RA2 aliases
#define IO_RA2_TRIS                 TRISAbits.TRISA2
#define IO_RA2_LAT                  LATAbits.LATA2
#define IO_RA2_PORT                 PORTAbits.RA2
#define IO_RA2_WPU                  WPUAbits.WPUA2
#define IO_RA2_OD                   ODCONAbits.ODCA2
#define IO_RA2_ANS                  ANSELAbits.ANSELA2
#define IO_RA2_SetHigh()            do { LATAbits.LATA2 = 1; } while(0)
#define IO_RA2_SetLow()             do { LATAbits.LATA2 = 0; } while(0)
#define IO_RA2_Toggle()             do { LATAbits.LATA2 = ~LATAbits.LATA2; } while(0)
#define IO_RA2_GetValue()           PORTAbits.RA2
#define IO_RA2_SetDigitalInput()    do { TRISAbits.TRISA2 = 1; } while(0)
#define IO_RA2_SetDigitalOutput()   do { TRISAbits.TRISA2 = 0; } while(0)
#define IO_RA2_SetPullup()          do { WPUAbits.WPUA2 = 1; } while(0)
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// get/set RA5 aliases
#define RA5_IN2_TRIS                 TRISAbits.TRISA5
#define RA5_IN2_LAT                  LATAbits.LATA5
#define RA5_IN2_PORT                 PORTAbits.RA5
#define RA5_IN2_WPU                  WPUAbits.WPUA5
#define RA5_IN2_OD                   ODCONAbits.ODCA5
#define RA5_IN2_ANS                  ANSELAbits.ANSELA5
#define RA5_IN2_SetHigh()            do { LATAbits.LATA5 = 1; } while(0)
#define RA5_IN2_SetLow()             do { LATAbits.LATA5 = 0; } while(0)
#define RA5_IN2_Toggle()             do { LATAbits.LATA5 = ~LATAbits.LATA5; } while(0)
#define RA5_IN2_GetValue()           PORTAbits.RA5
#define RA5_IN2_SetDigitalInput()    do { TRISAbits.TRISA5 = 1; } while(0)
#define RA5_IN2_SetDigitalOutput()   do { TRISAbits.TRISA5 = 0; } while(0)
#define RA5_IN2_SetPullup()          do { WPUAbits.WPUA5 = 1; } while(0)
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// get/set RB2 aliases
#define MSGEQ_RESET_TRIS                 TRISBbits.TRISB2
#define MSGEQ_RESET_LAT                  LATBbits.LATB2
#define MSGEQ_RESET_PORT                 PORTBbits.RB2
#define MSGEQ_RESET_WPU                  WPUBbits.WPUB2
#define MSGEQ_RESET_OD                   ODCONBbits.ODCB2
#define MSGEQ_RESET_ANS                  ANSELBbits.ANSELB2
#define MSGEQ_RESET_SetHigh()            do { LATBbits.LATB2 = 1; } while(0)
#define MSGEQ_RESET_SetLow()             do { LATBbits.LATB2 = 0; } while(0)
#define MSGEQ_RESET_Toggle()             do { LATBbits.LATB2 = ~LATBbits.LATB2; } while(0)
#define MSGEQ_RESET_GetValue()           PORTBbits.RB2
#define MSGEQ_RESET_SetDigitalInput()    do { TRISBbits.TRISB2 = 1; } while(0)
#define MSGEQ_RESET_SetDigitalOutput()   do { TRISBbits.TRISB2 = 0; } while(0)
#define MSGEQ_RESET_SetPullup()          do { WPUBbits.WPUB2 = 1; } while(0)
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// get/set RB3 aliases
#define MSGEQ_STROBE_TRIS                 TRISBbits.TRISB3
#define MSGEQ_STROBE_LAT                  LATBbits.LATB3
#define MSGEQ_STROBE_PORT                 PORTBbits.RB3
#define MSGEQ_STROBE_WPU                  WPUBbits.WPUB3
#define MSGEQ_STROBE_OD                   ODCONBbits.ODCB3
#define MSGEQ_STROBE_ANS                  ANSELBbits.ANSELB3
#define MSGEQ_STROBE_SetHigh()            do { LATBbits.LATB3 = 1; } while(0)
#define MSGEQ_STROBE_SetLow()             do { LATBbits.LATB3 = 0; } while(0)
#define MSGEQ_STROBE_Toggle()             do { LATBbits.LATB3 = ~LATBbits.LATB3; } while(0)
#define MSGEQ_STROBE_GetValue()           PORTBbits.RB3
#define MSGEQ_STROBE_SetDigitalInput()    do { TRISBbits.TRISB3 = 1; } while(0)
#define MSGEQ_STROBE_SetDigitalOutput()   do { TRISBbits.TRISB3 = 0; } while(0)
#define MSGEQ_STROBE_SetPullup()          do { WPUBbits.WPUB3 = 1; } while(0)
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// get/set RB4 aliases
#define IO_RB4_TRIS                 TRISBbits.TRISB4
#define IO_RB4_LAT                  LATBbits.LATB4
#define IO_RB4_PORT                 PORTBbits.RB4
#define IO_RB4_WPU                  WPUBbits.WPUB4
#define IO_RB4_OD                   ODCONBbits.ODCB4
#define IO_RB4_ANS                  ANSELBbits.ANSELB4
#define IO_RB4_SetHigh()            do { LATBbits.LATB4 = 1; } while(0)
#define IO_RB4_SetLow()             do { LATBbits.LATB4 = 0; } while(0)
#define IO_RB4_Toggle()             do { LATBbits.LATB4 = ~LATBbits.LATB4; } while(0)
#define IO_RB4_GetValue()           PORTBbits.RB4
#define IO_RB4_SetDigitalInput()    do { TRISBbits.TRISB4 = 1; } while(0)
#define IO_RB4_SetDigitalOutput()   do { TRISBbits.TRISB4 = 0; } while(0)
#define IO_RB4_SetPullup()          do { WPUBbits.WPUB4 = 1; } while(0)
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// get/set RE0 aliases
#define IO_RE0_TRIS                 TRISEbits.TRISE0
#define IO_RE0_LAT                  LATEbits.LATE0
#define IO_RE0_PORT                 PORTEbits.RE0
#define IO_RE0_WPU                  WPUEbits.WPUE0
#define IO_RE0_OD                   ODCONEbits.ODCE0
#define IO_RE0_ANS                  ANSELEbits.ANSELE0
#define IO_RE0_SetHigh()            do { LATEbits.LATE0 = 1; } while(0)
#define IO_RE0_SetLow()             do { LATEbits.LATE0 = 0; } while(0)
#define IO_RE0_Toggle()             do { LATEbits.LATE0 = ~LATEbits.LATE0; } while(0)
#define IO_RE0_GetValue()           PORTEbits.RE0
#define IO_RE0_SetDigitalInput()    do { TRISEbits.TRISE0 = 1; } while(0)
#define IO_RE0_SetDigitalOutput()   do { TRISEbits.TRISE0 = 0; } while(0)
#define IO_RE0_SetPullup()          do { WPUEbits.WPUE0 = 1; } while(0)
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
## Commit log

2023-08-09 MPAE-16207 initial commit
2023-08-09 MPAE-16207 added CI support and readme
2023-10-05 MPAE-16207: Initial commit
2023-10-05 MPAE-16207: Updated readme
2023-10-05 MPAE-16207: Updated readm
2023-10-05 MPAE-16207: Updated metadata
2023-10-06 MPAE-16207: README review changes implemented
2023-10-09 MPAE-16207: Updated readme, rename folders
2023-10-10 MPAE-16763: Add newline

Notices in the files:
DMX512_Receiver.X/mcc_generated_files/system/pins.h:
© [2023] Microchip Technology Inc. and its subsidiaries.
